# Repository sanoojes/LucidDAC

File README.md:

# LucidDAC

A USB-C to 3.5mm DAC cuzz new phones doesn't come with a 3.5mm Jack(f Apple for
removing so that the industry follows)

## PCB

## Bill of Materials

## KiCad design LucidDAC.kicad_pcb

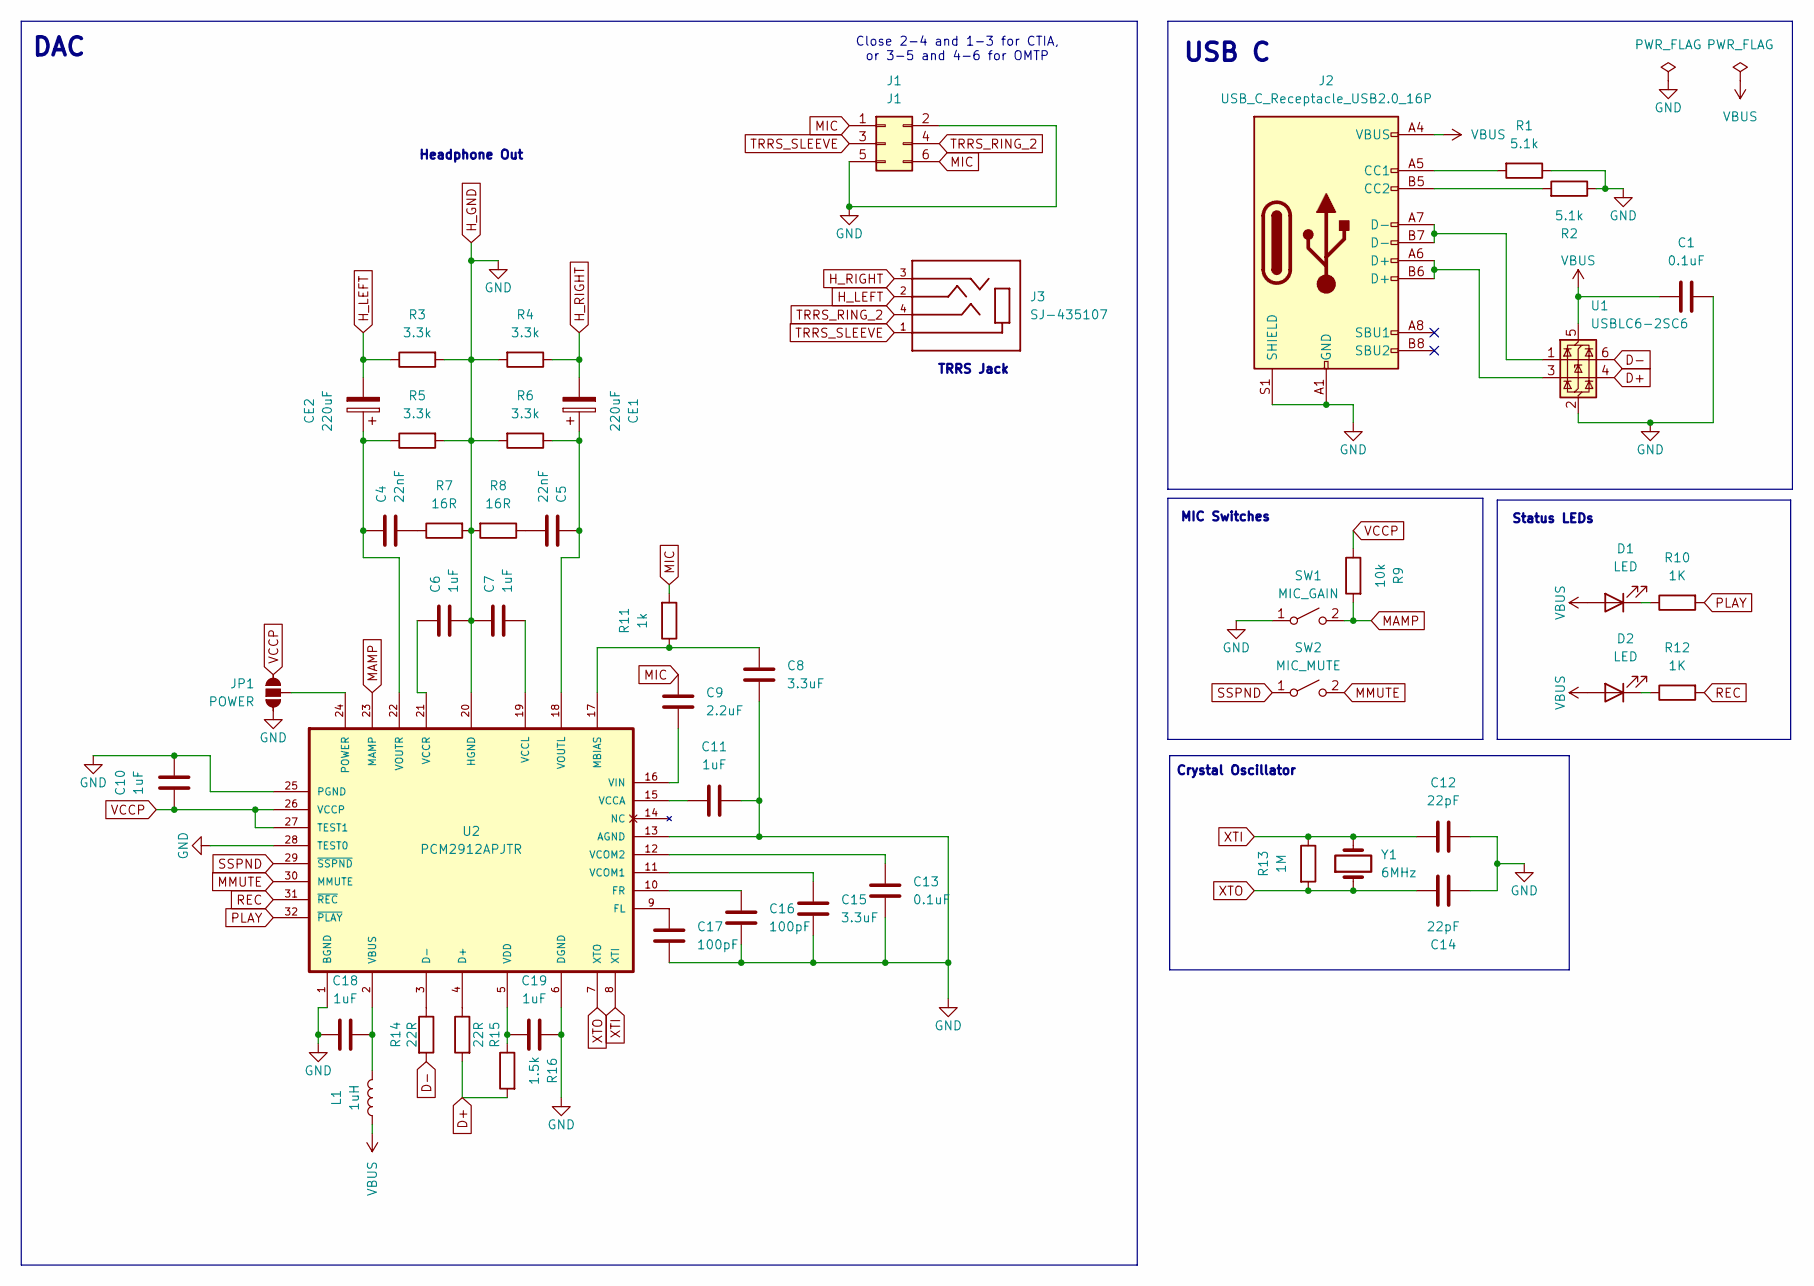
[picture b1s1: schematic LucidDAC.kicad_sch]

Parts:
C1, C13: 0.1uF; C_0805_2012Metric_Pad1.18x1.45mm_HandSolder
C4, C5: 22nF; C_0805_2012Metric_Pad1.18x1.45mm_HandSolder
C6, C7, C10, C11, C18, C19: 1uF; C_0805_2012Metric_Pad1.18x1.45mm_HandSolder
C8, C15: 3.3uF; C_0805_2012Metric_Pad1.18x1.45mm_HandSolder
C9: 2.2uF; CAP_EEEHB1H2R2R
C12, C14: 22pF; C_0805_2012Metric_Pad1.18x1.45mm_HandSolder
C16, C17: 100pF; C_0805_2012Metric_Pad1.18x1.45mm_HandSolder
CE1, CE2: 220uF; CAP_EEEFK1A221XP
D1, D2: LED; LED_0805_2012Metric
J1: J1; PinHeader_2x03_P2.54mm_Vertical
J2: USB_C_Receptacle_USB2.0_16P; USB_C_Receptacle_HRO_TYPE-C-31-M-23
J3: SJ-435107; CUI_SJ-435107
JP1: POWER; SolderJumper-3_P1.3mm_Open_RoundedPad1.0x1.5mm
L1: 1uH; L_0805_2012Metric_Pad1.05x1.20mm_HandSolder
R1, R2: 5.1k; R_0805_2012Metric_Pad1.20x1.40mm_HandSolder
R3, R4, R5, R6: 3.3k; R_0805_2012Metric_Pad1.20x1.40mm_HandSolder
R7, R8: 16R; R_0805_2012Metric_Pad1.20x1.40mm_HandSolder
R9: 10k; R_0805_2012Metric_Pad1.20x1.40mm_HandSolder
R10, R12: 1K; R_0805_2012Metric_Pad1.20x1.40mm_HandSolder
R11: 1k; R_0805_2012Metric_Pad1.20x1.40mm_HandSolder
R13: 1M; R_0805_2012Metric_Pad1.20x1.40mm_HandSolder
R14, R15: 22R; R_0805_2012Metric_Pad1.20x1.40mm_HandSolder
R16: 1.5k; R_0805_2012Metric_Pad1.20x1.40mm_HandSolder
SW1: MIC_GAIN; PinHeader_1x02_P2.54mm_Vertical
SW2: MIC_MUTE; PinHeader_1x02_P2.54mm_Vertical
U1: USBLC6-2SC6; SOT-23-6
U2: PCM2912APJTR; QFP80P900X900X120-32N
Y1: 6MHz; Crystal_HC49-4H_Vertical

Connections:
D+: R15.2, R16.2, U1.4 (I/O2)
D-: R14.2, U1.6 (I/O1)
H_GND: C1.2, C6.1, C7.2, C8.1, C10.2, C11.1, C12.1, C13.2, C14.1, C15.2, C16.2, C17.2, C18.1, C19.2, J1.2, J1.5, J2.A1 (GND), J2.A12 (GND), J2.B1 (GND), J2.B12 (GND), J2.S1 (SHIELD), JP1.1 (A), R1.1, R2.1, R3.2, R4.2, R5.2, R6.2, R7.2, R8.2, SW1.1 (A), U1.2 (GND), U2.1 (BGND), U2.6 (DGND), U2.13 (AGND), U2.20 (HGND), U2.25 (PGND), U2.28 (TEST0); also elsewhere on the board
H_LEFT: CE2.2, J3.2, R3.1
H_RIGHT: CE1.2, J3.3, R4.1
MAMP: R9.2, SW1.2 (B), U2.23 (MAMP); also elsewhere on the board
MIC: C9.1, J1.1, J1.6, R11.2
MMUTE: SW2.2 (B), U2.30 (MMUTE); also elsewhere on the board
unnamed: C4.1, R7.1
unnamed: C5.1, R8.1
unnamed: D1.1 (K), R10.1
unnamed: D2.1 (K), R12.1
unnamed: J2.A5 (CC1), R1.2
unnamed: J2.B5 (CC2), R2.2
unnamed: J2.A6 (D+), J2.B6 (D+), U1.3 (I/O2)
unnamed: J2.A7 (D-), J2.B7 (D-), U1.1 (I/O1)
unnamed: JP1.2 (B), U2.24 (POWER)
unnamed: R15.1, U2.4 (D+)
unnamed: R14.1, U2.3 (D-)
unnamed: C17.1, U2.9 (FL)
unnamed: C16.1, U2.10 (FR)
unnamed: C8.2, R11.1, U2.17 (MBIAS)
unnamed: C18.2, L1.1, U2.2 (VBUS)
unnamed: C11.2, U2.15 (VCCA)
unnamed: C7.1, U2.19 (VCCL)
unnamed: C6.2, U2.21 (VCCR)
unnamed: C15.1, U2.11 (VCOM1)
unnamed: C13.1, U2.12 (VCOM2)
unnamed: C19.1, R16.1, U2.5 (VDD)
unnamed: C9.2, U2.16 (VIN)
unnamed: C5.2, CE1.1, R6.1, U2.18 (VOUTL)
unnamed: C4.2, CE2.1, R5.1, U2.22 (VOUTR)
PLAY: R10.2, U2.32 (~PLAY)
REC: R12.2, U2.31 (~REC)
SSPND: SW2.1 (A), U2.29 (~SSPND); also elsewhere on the board
TRRS_RING_2: J1.4, J3.4
TRRS_SLEEVE: J1.3, J3.1
VBUS: C1.1, D1.2 (A), D2.2 (A), J2.A4 (VBUS), J2.A9 (VBUS), J2.B4 (VBUS), J2.B9 (VBUS), L1.2, U1.5 (VBUS)
VCCP: C10.1, JP1.3 (C), R9.1, U2.26 (VCCP), U2.27 (TEST1)
XTI: C12.2, R13.1, U2.8 (XTI), Y1.2
XTO: C14.2, R13.2, U2.7 (XTO), Y1.1

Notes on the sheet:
Headphone Out
USB C
Close 2-4 and 1-3 for CTIA, or 3-5 and 4-6 for OMTP
Status LEDs
Crystal Oscillator
DAC
TRRS Jack
MIC Switches

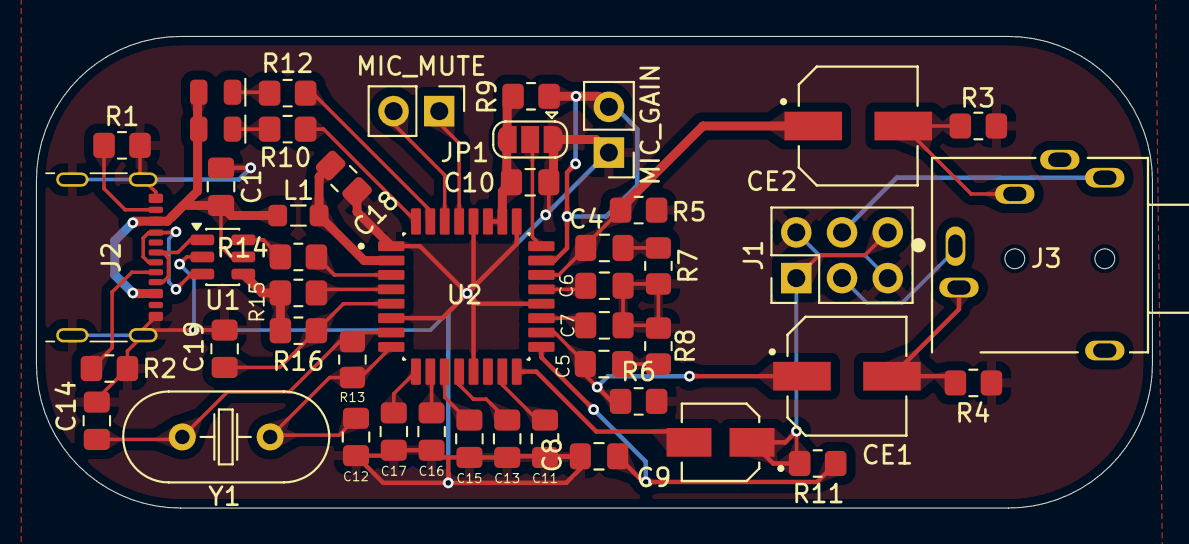
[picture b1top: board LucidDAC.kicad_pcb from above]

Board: 2 copper layers, 62.0 x 26.2 mm, 48 parts (1 on the bottom side), 41 nets.

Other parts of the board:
MIC_GAIN: MIC_GAIN; PinHeader_1x02_P2.54mm_Vertical
MIC_MUTE: MIC_MUTE; PinHeader_1x02_P2.54mm_Vertical
ref: LOGO

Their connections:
H_GND: MIC_GAIN.1 (A); also elsewhere on the board
MAMP: MIC_GAIN.2 (B); also elsewhere on the board
MMUTE: MIC_MUTE.2 (B); also elsewhere on the board
SSPND: MIC_MUTE.1 (A); also elsewhere on the board

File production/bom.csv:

Designator,Footprint,Quantity,Value,LCSC Part #
"C1, C13",0805,2,0.1uF,
"C10, C11, C18, C19, C6, C7",0805,6,1uF,
"C12, C14",0805,2,22pF,
"C15, C8",0805,2,3.3uF,
"C16, C17",0805,2,100pF,
"C4, C5",0805,2,22nF,
C9,CAP_EEEHB1H2R2R,1,2.2uF,
"CE1, CE2",CAP_EEEFK1A221XP,2,220uF,
"D1, D2",0805,2,LED,
J1,PinHeader_2x03_P2.54mm_Vertical,1,J1,
J2,USB_C_Receptacle_HRO_TYPE-C-31-M-23,1,USB_C_Receptacle_USB2.0_16P,
J3,CUI_SJ-435107,1,SJ-435107,
JP1,SolderJumper-3_P1.3mm_Open_RoundedPad1.0x1.5mm,1,POWER,
L1,0805,1,1uH,
MIC_GAIN,PinHeader_1x02_P2.54mm_Vertical,1,MIC_GAIN,
MIC_MUTE,PinHeader_1x02_P2.54mm_Vertical,1,MIC_MUTE,
"R1, R2",0805,2,5.1k,
"R10, R11, R12",0805,3,1K,
R13,0805,1,1M,
"R14, R15",0805,2,22R,
R16,0805,1,1.5k,
"R3, R4, R5, R6",0805,4,3.3k,
"R7, R8",0805,2,16R,
R9,0805,1,10k,
U1,SOT-23-6,1,USBLC6-2SC6,
U2,QFP80P900X900X120-32N,1,PCM2912APJTR,
Y1,Crystal_HC49-4H_Vertical,1,6MHz,

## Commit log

2025-12-28 init: initial commit
2025-12-28 add bom.csv
2025-12-28 update bom
2025-12-28 update pcb
2025-12-28 fix: bom total value
